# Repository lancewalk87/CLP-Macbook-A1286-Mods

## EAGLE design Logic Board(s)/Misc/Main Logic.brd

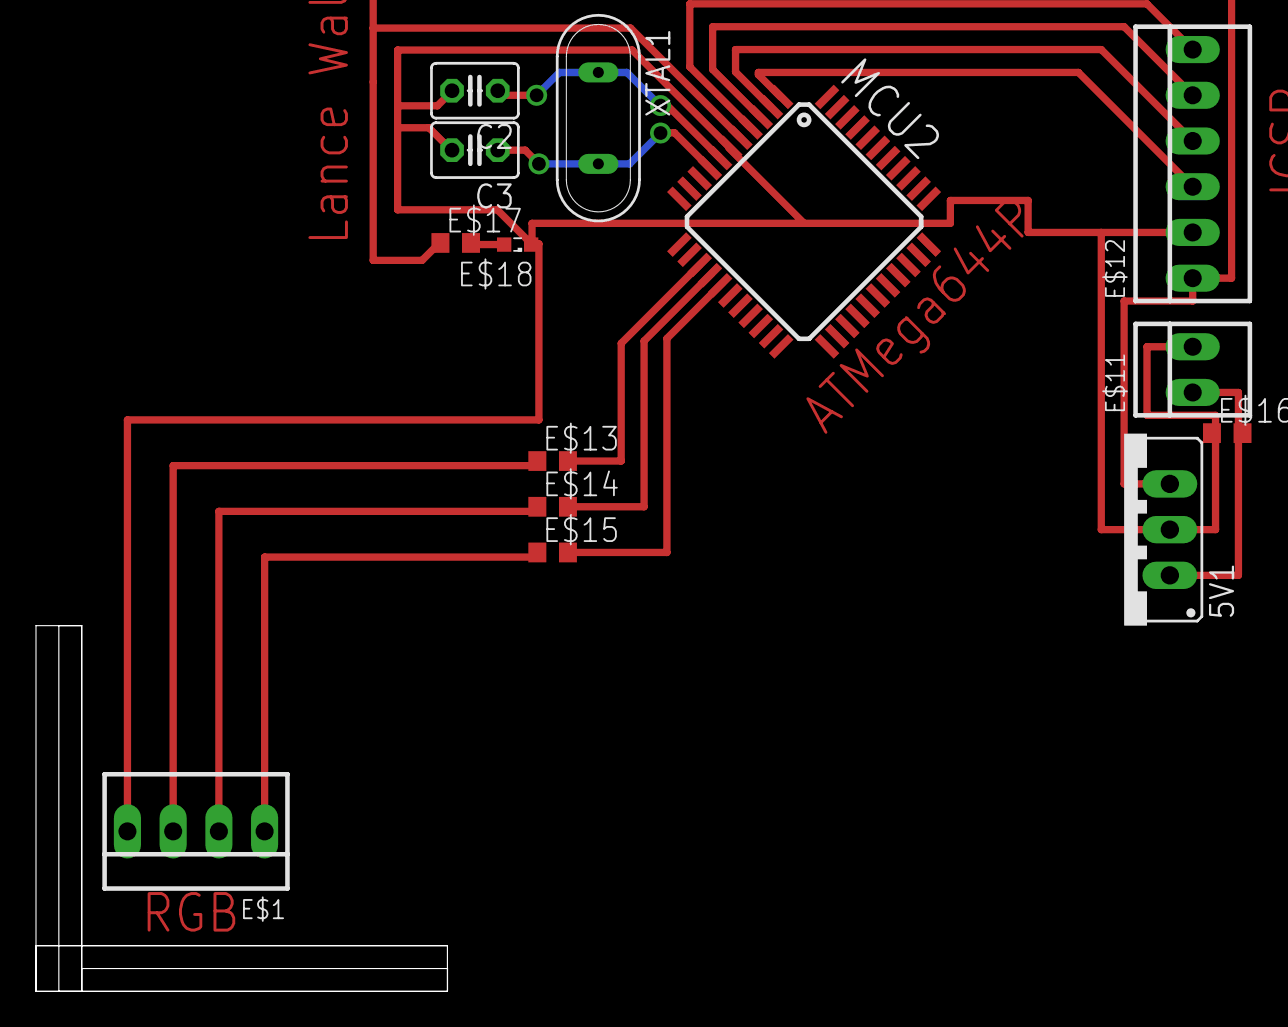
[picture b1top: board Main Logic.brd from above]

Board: 2 copper layers, 14 parts (0 on the bottom side), 5 nets.

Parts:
5V1: 78XXS
C2, C3: C025-030X050
E$1: 22-23-2041
E$11: 22-23-2021
E$12: 22-23-2061
E$13, E$14, E$15, E$16, E$17: R0603
E$18: LED_SML0603
MCU2: TQFP44
XTAL1: QS

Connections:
GND1: 5V1.GND, E$1.4, E$11.2, E$12.2
INPUT1: 5V1.IN, E$11.1
MOSI2: C2.1, XTAL1.1
MOSI3: C3.1, XTAL1.2
VCC1: 5V1.OUT, E$12.1

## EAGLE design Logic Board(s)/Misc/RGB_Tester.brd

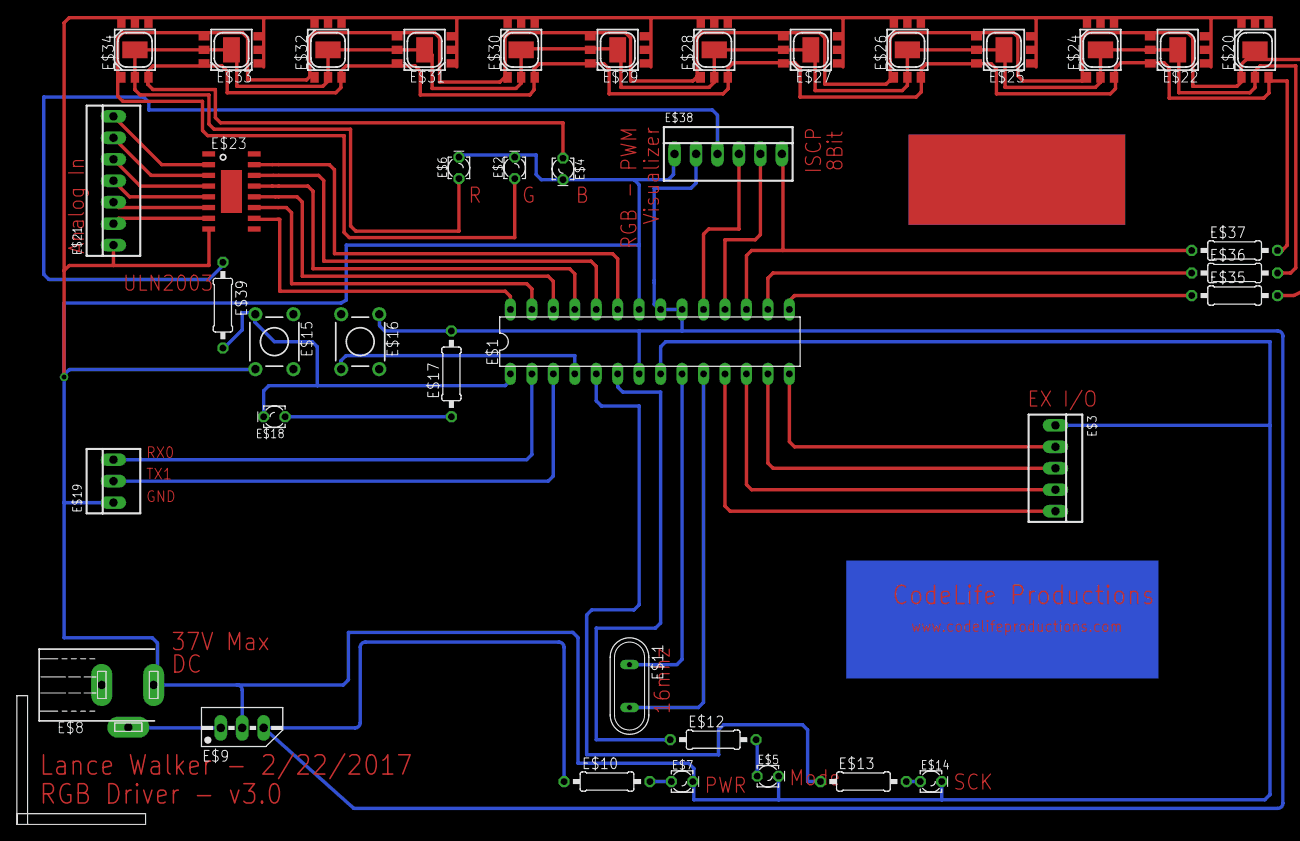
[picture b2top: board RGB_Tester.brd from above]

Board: 2 copper layers, 39 parts (0 on the bottom side), 18 nets.

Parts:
E$1: DIL28-3
E$2, E$4, E$5, E$6, E$7, E$14, E$18: LED_LD260
E$3: 22-23-2051
E$8: 733980-62
E$9: 78MXXS
E$10, E$12, E$13, E$17, E$35, E$36, E$37, E$39: 0207/10
E$11: QS
E$15, E$16: TL1105
E$19: 22-23-2031
E$20, E$22, E$24, E$25, E$26, E$27, E$28, E$29, E$30, E$31, E$32, E$33, E$34: LP2C63-ST-RGB-SR0
E$21: 22-23-2071
E$23: SOIC16
E$38: 22-23-2061

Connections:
BLUE: E$4.A, E$37.1, E$37.2
GND: E$1.8, E$1.22, E$3.1, E$5.K, E$9.GND, E$14.K, E$19.1, E$38.1
GREEN: E$2.A, E$35.1
MODE_LED: E$1.6, E$5.A, E$12.1
MOSI: E$1.18, E$38.5
PWR: E$1.7, E$1.20, E$1.21, E$7.A, E$9.IN, E$9.OUT, E$10.1, E$10.2, E$38.2
RED: E$6.A, E$36.1, E$36.2
RESET: E$1.1, E$18.K, E$38.3, E$39.1
S$1: E$17.1, E$18.A
S$2: E$1.11, E$3.5
S$4: E$1.12, E$3.4
S$5: E$1.13, E$3.3
S$6: E$1.14, E$3.2
SCK: E$1.19, E$38.4
SCK_MODE: E$1.5, E$13.1, E$13.2
TX: E$1.3, E$19.2
XTAL1: E$1.9, E$11.1
XTAL2: E$1.10, E$11.2

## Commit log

2018-11-02 v1.0.0
